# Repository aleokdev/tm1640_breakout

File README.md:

# TM1640 Breakout Board
A breakout board made for the chinese Titan Micro Electronics TM1640 chip, commonly used in cheap 7-segment displays.

The board has been designed mostly with size in mind to be able to plug it into a breadboard. It is 14x8 breadboard pins long (1.4x0.8in, or around 35.56x20.32mm). It follows the datasheet design (Using both a 10k pullup resistor and 100p capacitor for both data lines, and a 100nF as well as a 100uF capacitor for the VCC pin).

Contributions as well as criticism and suggestions are more than welcome.

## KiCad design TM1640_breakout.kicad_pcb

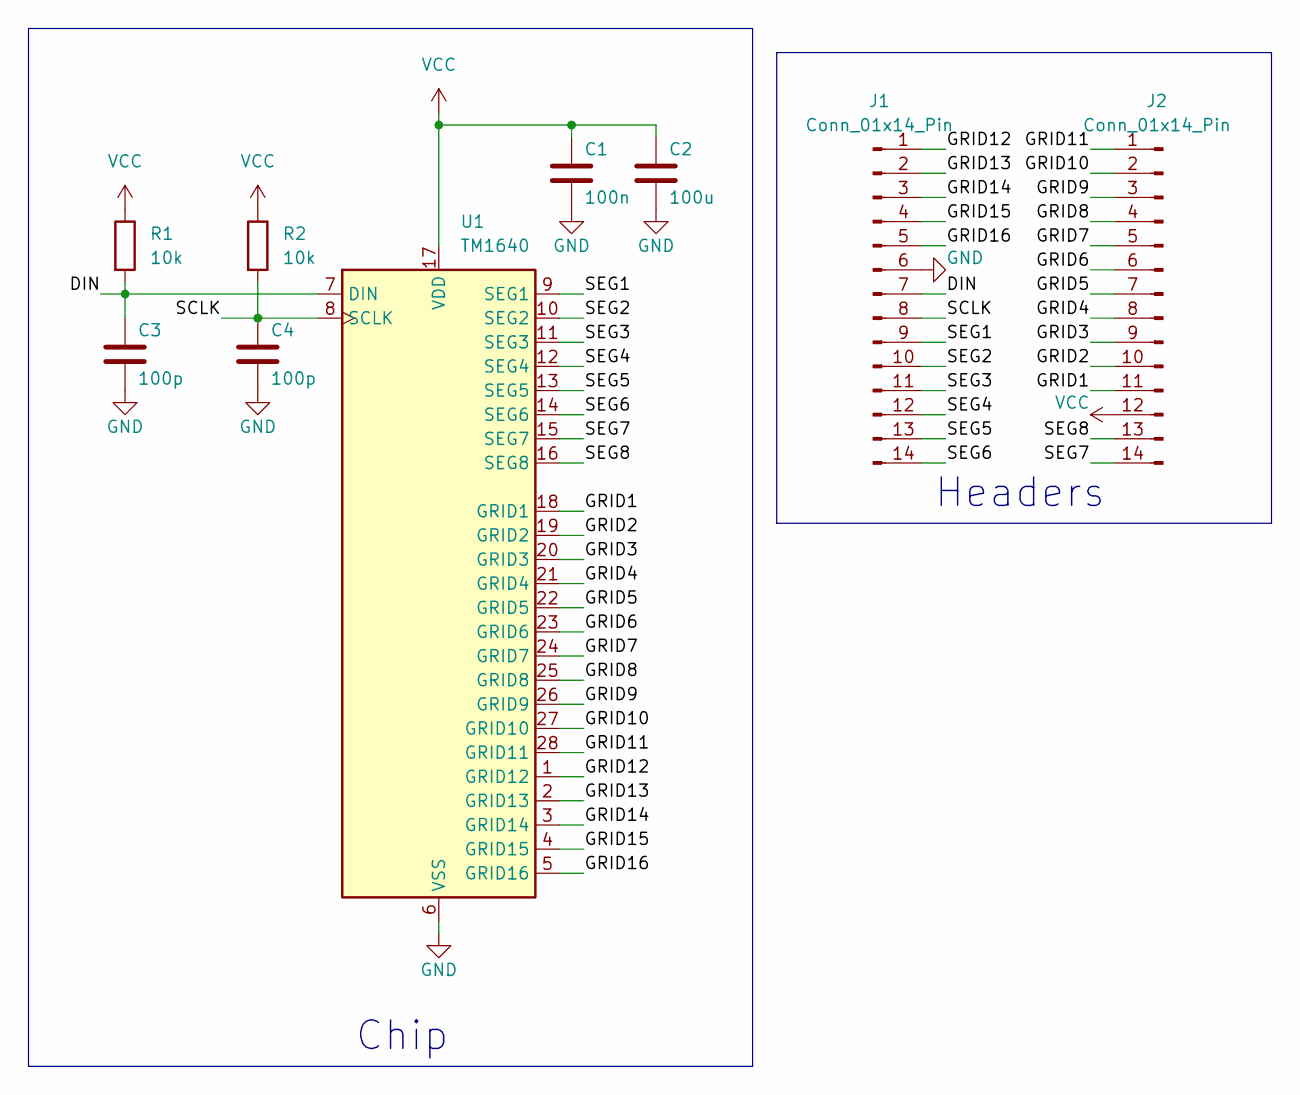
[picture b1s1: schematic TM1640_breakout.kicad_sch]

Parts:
C1: 100n; C_0402_1005Metric
C2: 100u; C_0603_1608Metric
C3, C4: 100p; C_0402_1005Metric
J1, J2: Conn_01x14_Pin; PinHeader_1x14_P2.54mm_Vertical
R1, R2: 10k; R_0402_1005Metric
U1: TM1640; SOIC-28W_7.5x17.9mm_P1.27mm

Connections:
/DIN: C3.1, J1.7, R1.2, U1.7 (DIN)
/GRID1: J2.11, U1.18 (GRID1)
/GRID2: J2.10, U1.19 (GRID2)
/GRID3: J2.9, U1.20 (GRID3)
/GRID4: J2.8, U1.21 (GRID4)
/GRID5: J2.7, U1.22 (GRID5)
/GRID6: J2.6, U1.23 (GRID6)
/GRID7: J2.5, U1.24 (GRID7)
/GRID8: J2.4, U1.25 (GRID8)
/GRID9: J2.3, U1.26 (GRID9)
/GRID10: J2.2, U1.27 (GRID10)
/GRID11: J2.1, U1.28 (GRID11)
/GRID12: J1.1, U1.1 (GRID12)
/GRID13: J1.2, U1.2 (GRID13)
/GRID14: J1.3, U1.3 (GRID14)
/GRID15: J1.4, U1.4 (GRID15)
/GRID16: J1.5, U1.5 (GRID16)
/SCLK: C4.1, J1.8, R2.2, U1.8 (SCLK)
/SEG1: J1.9, U1.9 (SEG1)
/SEG2: J1.10, U1.10 (SEG2)
/SEG3: J1.11, U1.11 (SEG3)
/SEG4: J1.12, U1.12 (SEG4)
/SEG5: J1.13, U1.13 (SEG5)
/SEG6: J1.14, U1.14 (SEG6)
/SEG7: J2.14, U1.15 (SEG7)
/SEG8: J2.13, U1.16 (SEG8)
GND: C1.2, C2.2, C3.2, C4.2, J1.6, U1.6 (VSS)
VCC: C1.1, C2.1, J2.12, R1.1, R2.1, U1.17 (VDD)

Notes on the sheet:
Chip
Headers

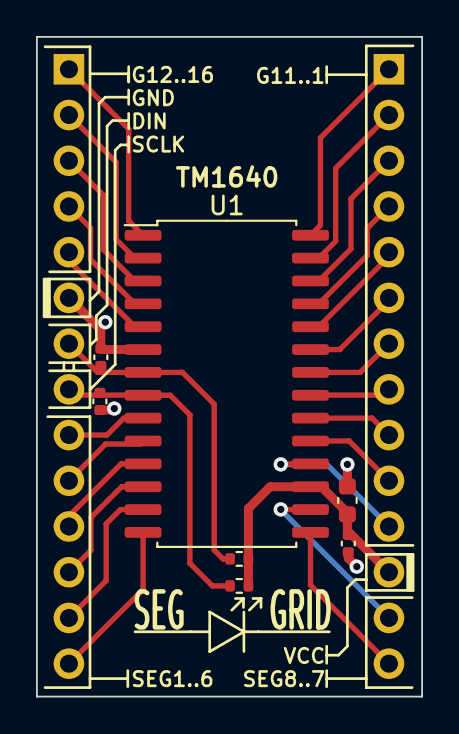
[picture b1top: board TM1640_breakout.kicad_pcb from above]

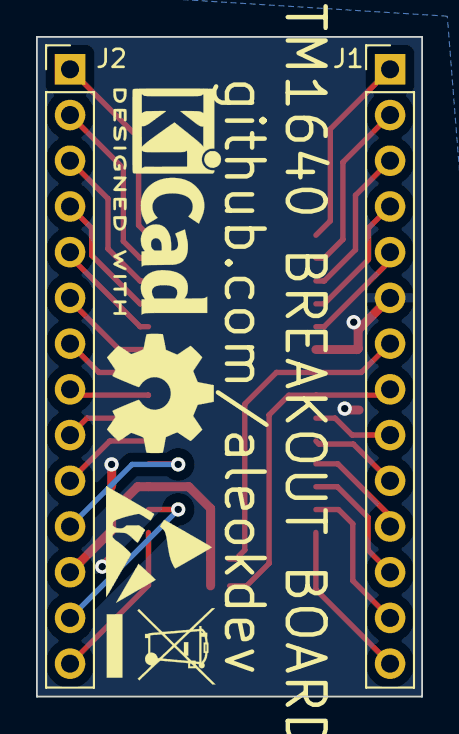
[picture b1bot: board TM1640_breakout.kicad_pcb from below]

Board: 2 copper layers, 21.4 x 36.6 mm, 9 parts (2 on the bottom side), 28 nets.

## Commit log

2023-09-23 Upload preview image
